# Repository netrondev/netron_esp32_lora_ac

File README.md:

# ESP32 LoRaWAN AC current monitor

A mains current monitor built on an ESP32 and an SX1262 radio. It measures AC
current through an ACS712 hall-effect sensor and reports it over LoRaWAN as an
OTAA Class A device. The repo also includes a small network server so you can
receive the reports and configure devices remotely, plus the KiCad hardware.

Everything is written in Rust except the payload codec, which is plain
JavaScript so it can be pasted into ChirpStack, The Things Network or Node-RED.

## How the pieces fit together

```
ACS712 current sensor
  └─ ESP32 + SX1262           firmware/           OTAA Class A device
       ~ 868.1 MHz SF7 ~
  └─ Milesight UG63 gateway                       Semtech UDP packet forwarder
       └─ software/lorans                         network server: joins, keys,
                                                  uplink decode, downlink queue
```

The gateway's own network server is **not** used. It has no usable downlink
route: there's no HTTP endpoint, and its MQTT application forwarder reboots the
gateway. Without downlinks there's no remote configuration. So the gateway runs
as a plain packet forwarder, and `software/lorans` does the network server's
job. `software/lorans/README.md` has the details.

Any gateway that speaks the Semtech UDP protocol should work in place of the
UG63. Alternatively, the devices can join a standard network server such as
ChirpStack, using the codec in `software/loradecode`.

| Directory | What it is |
|---|---|
| `firmware/` | ESP32 firmware. Measures current, joins by OTAA, reports aggregated min/avg/max, applies configuration downlinks |
| `software/lorans/` | Network server. Run this to receive uplinks and send commands |
| `software/loradecode/` | JavaScript payload decoder and command encoder for ChirpStack, TTN or Node-RED |
| `software/milesight_d4/` | Milesight gateway HTTP client: status, device list, forwarder mode, payload decode/encode |
| `software/loramqtt/` | Minimal MQTT broker, kept for diagnosing the gateway's MQTT forwarding |
| `docs/PROTOCOL.md` | Uplink channel map and downlink command set |
| `diagram/` | System overview: power supply, sensing, MCU and radio |
| `hardware/` | KiCad schematics, PCBs and JLCPCB fabrication outputs |
| `scripts/` | Build, flash and monitor helpers |

## Hardware

- **MCU:** ESP32 Mini32 (Wemos D1 Mini ESP32 form factor)
- **Radio:** Ai-Thinker Ra-01SH (SX1262), 868 MHz
- **Sensor:** ACS712-20A on GPIO34 through a voltage divider. RMS current is
  computed over one 50 Hz cycle of oversampled ADC readings
- **Power:** MB10S bridge rectifier into a BP2525 non-isolated buck, 5 V from
  230 V mains

| SX1262 | ESP32 |
|---|---|
| NSS | GPIO5 |
| RESET | GPIO27 |
| DIO1 | GPIO26 |
| SCK | GPIO18 |
| MISO | GPIO19 |
| MOSI | GPIO23 |

BUSY isn't wired to the ESP32. The driver waits a fixed settling time after
each command instead, and detects TxDone/RxDone from DIO1. The status LED is
on GPIO2.

> **Warning:** the power supply is non-isolated, so the whole board sits at
> mains potential. Don't touch it or connect USB while it's powered from
> mains.

## Device identity and keys

| | |
|---|---|
| DevEUI | Derived from the ESP32's MAC: `OUI FF FE NIC` |
| JoinEUI | `0000000000000000` |
| AppKey | The DevEUI repeated, e.g. `E08CFEFFFE34C3AC` → `E08CFEFFFE34C3ACE08CFEFFFE34C3AC` |

This follows the Milesight convention, so a device can be onboarded from
nothing but its join request. It also means **the AppKey is not a secret**.
That's fine for a private network on a private gateway. If you need real
over-the-air security, give each device a random AppKey. `docs/PROTOCOL.md`
covers this, along with the payload format.

## Getting started

### Toolchain

The ESP32 needs Rust's Xtensa toolchain. Install it with
[espup](https://github.com/esp-rs/espup), which writes `~/export-esp.sh`, then
install `espflash`:

```bash
cargo install espup espflash
espup install
```

Alternatively, build inside Docker with the image in `firmware/`. `scripts/build.sh`
and `scripts/flash.sh` use it:

```bash
docker build -t esp32-rust firmware/
```

### Flash and monitor a device

The scripts find the serial port automatically, or you can pass it explicitly:

```bash
./scripts/flash_native.sh            # host toolchain: build, flash, print the MAC
./scripts/flash.sh /dev/ttyUSB0      # same, building in Docker
./scripts/monitor.sh                 # serial monitor in Docker (CTRL+R resets, CTRL+C exits)
```

### Run the network server

Point the gateway's packet forwarder at this host on UDP port 1700, then start
the network server:

```bash
cargo run --manifest-path software/lorans/Cargo.toml
```

It accepts joins, decodes uplinks and queues downlinks. Commands go to a
control socket on `127.0.0.1:7788`. A queued downlink is sent in the receive
window after the device's next uplink. Intervals are in seconds:

```bash
echo 'downlink E08CFEFFFE34C3AC report=60 sample=5 jitter=10' | nc -q1 127.0.0.1 7788
echo 'list' | nc -q1 127.0.0.1 7788
```

### Milesight gateway

Copy `software/milesight_d4/config.json.example` to `config.json` and add the
gateway's address and login. Then:

```bash
cargo run --manifest-path software/milesight_d4/Cargo.toml -- status
cargo run --manifest-path software/milesight_d4/Cargo.toml -- set-forwarder semtech 192.168.1.100
```

## Firmware behaviour

- Joins by OTAA, retrying with exponential backoff
- Samples current every `sample` seconds and accumulates min/avg/max
- Sends one confirmed, aggregated report every `report` seconds, offset by a
  random ± `jitter` seconds so devices don't collide. An unacknowledged
  report is retried once
- Re-joins if the network stops acknowledging
- Applies configuration downlinks (intervals, jitter, reboot) and echoes each
  applied setting back as confirmation
- Keeps cumulative energy (mAh), frame counters, the join nonce and its
  configuration in flash across power cycles

### LED

| Pattern | Meaning |
|---|---|
| Short blink every ~0.5 s | Not joined yet, trying to join |
| Short blink per sample | Joined and measuring normally |
| Rapid triple blink | ADC error: sensor disconnected, or the reading saturated at 0 or 4095 |

## Troubleshooting

- **`xtensa-esp32-elf-gcc not found`:** run `source ~/export-esp.sh` first.
- **Permission denied on the serial port:** add yourself to the `dialout`
  group, or `sudo chmod 666 /dev/ttyUSB0`.
- **Device not found:** check `ls /dev/ttyUSB* /dev/ttyACM*`.
- **espflash asks for a chip or port inside Docker:** pass
  `--chip esp32 -p <port>` explicitly.
- **Flashing fails to connect:** hold BOOT while flashing, and release it
  after "Connecting...".

## License

Licensed under either of

- Apache License, Version 2.0 ([LICENSE-APACHE](LICENSE-APACHE))
- MIT license ([LICENSE-MIT](LICENSE-MIT))

at your option.

Unless you explicitly state otherwise, any contribution intentionally submitted
for inclusion in this work by you, as defined in the Apache-2.0 license, shall
be dual licensed as above, without any additional terms or conditions.

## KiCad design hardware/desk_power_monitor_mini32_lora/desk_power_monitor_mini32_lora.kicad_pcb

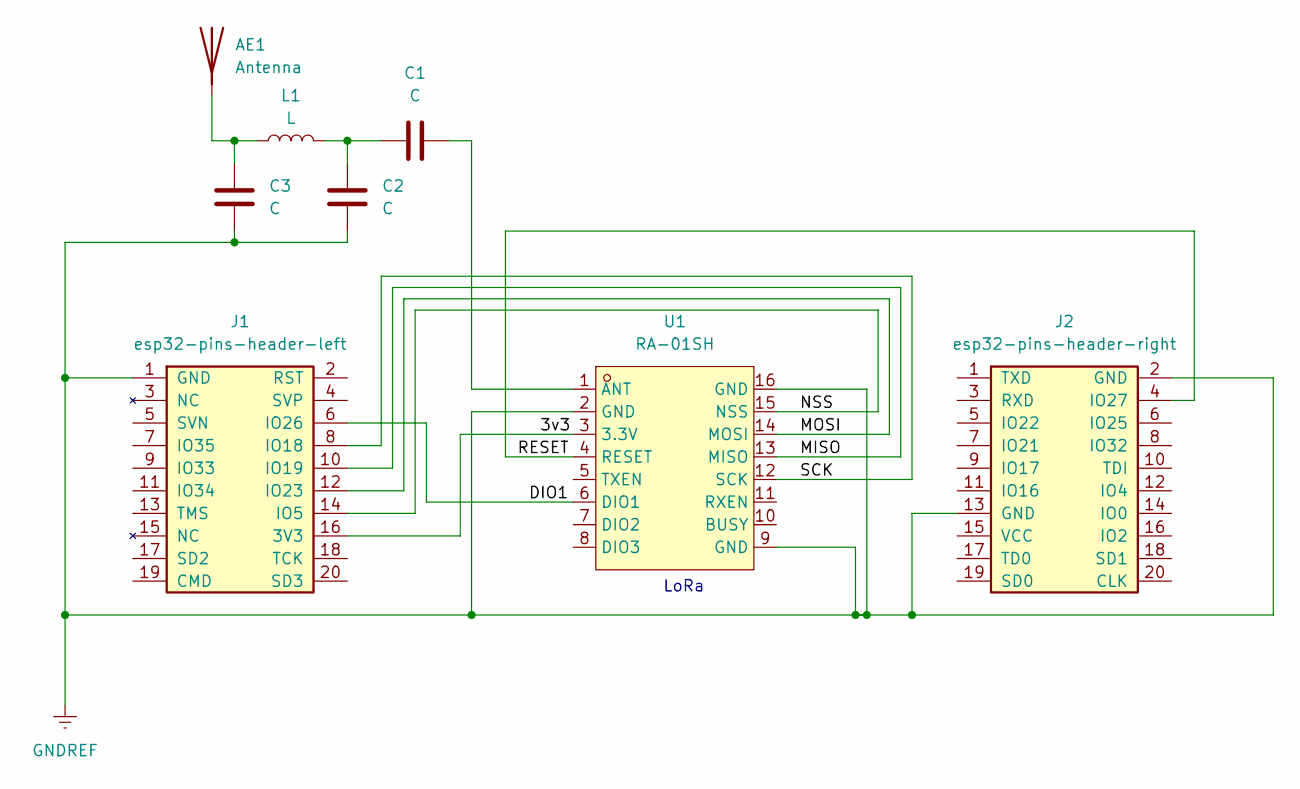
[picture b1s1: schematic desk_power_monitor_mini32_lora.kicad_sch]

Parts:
AE1: Antenna; Texas_SWRA416_868MHz_915MHz
C1, C2, C3: C; C_0805_2012Metric
J1: esp32-pins-header-left; PinHeader_2x10_P2.54mm_Vertical
J2: esp32-pins-header-right; PinHeader_2x10_P2.54mm_Vertical
L1: L; L_0805_2012Metric
U1: RA-01SH; WIRELM-SMD_RA-01SH; LCSC Part C2764087

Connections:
/3v3: J1.16 (3V3), U1.3 (3.3V)
/DIO1: J1.6 (IO26), U1.6 (DIO1)
/MISO: J1.10 (IO19), U1.13 (MISO)
/MOSI: J1.12 (IO23), U1.14 (MOSI)
/NSS: J1.14 (IO5), U1.15 (NSS)
/RESET: J2.4 (IO27), U1.4 (RESET)
/SCK: J1.8 (IO18), U1.12 (SCK)
GNDREF: C2.2, C3.2, J1.1 (GND), J2.2 (GND), J2.13 (GND), U1.2 (GND), U1.9 (GND), U1.16 (GND)
unnamed: AE1.1 (A), C3.1, L1.1
unnamed: C1.2, C2.1, L1.2
unnamed: C1.1, U1.1 (ANT)

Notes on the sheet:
LoRa

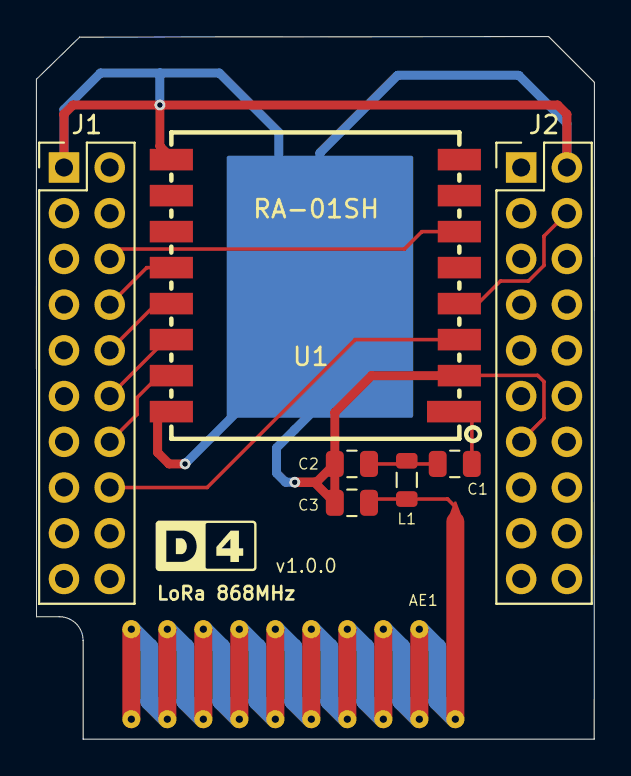
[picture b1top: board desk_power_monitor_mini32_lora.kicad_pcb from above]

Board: 2 copper layers, 31.0 x 39.0 mm, 8 parts (0 on the bottom side), 11 nets.

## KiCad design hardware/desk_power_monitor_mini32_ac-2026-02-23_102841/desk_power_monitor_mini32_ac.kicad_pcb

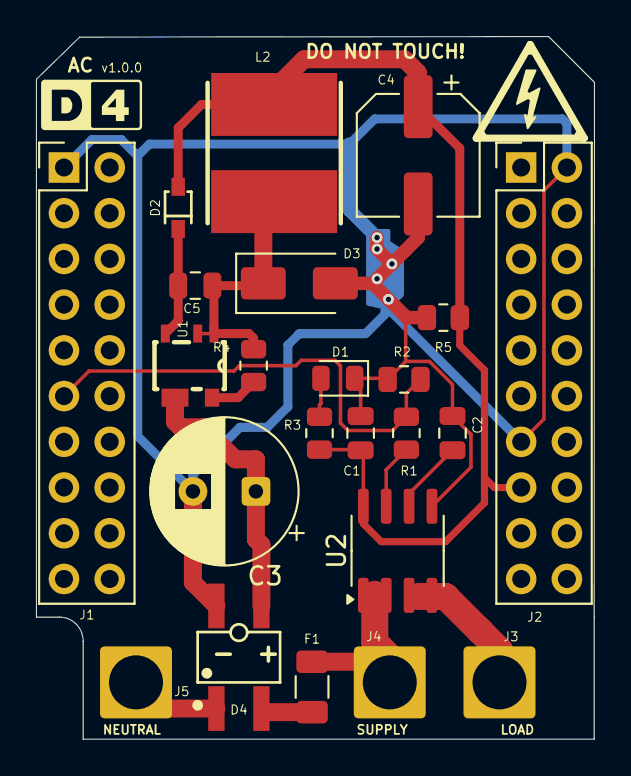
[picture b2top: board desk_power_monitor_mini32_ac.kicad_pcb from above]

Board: 2 copper layers, 31.0 x 39.0 mm, 23 parts (0 on the bottom side), 14 nets.

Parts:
C1, C5: 100nF; C_0805_2012Metric
C2: 1nF; C_0805_2012Metric
C3: 4.7µF / 400V electrolytic; CP_Radial_D8.0mm_P3.50mm
C4: 220uF/10V; CP_Elec_6.3x7.7
D1: LED; D_0805_2012Metric
D2: 1N4148WS-C57759; SOD-323_L1.8-W1.3-LS2.5-RD-1
D3: US1M; D_SMA
D4: MB10S(46MIL); MBS_L4.7-W4.0-P2.50-LS7.0-BL
F1: Fuse; Fuse_1206_3216Metric
J1: esp32-pins-header-left; PinHeader_2x10_P2.54mm_Vertical
J2: esp32-pins-header-right; PinHeader_2x10_P2.54mm_Vertical
J3: AC Live OUT; SolderWire-2.5sqmm_1x01_D2.4mm_OD3.6mm
J4: AC Live IN; SolderWire-2.5sqmm_1x01_D2.4mm_OD3.6mm
J5: AC Neutral IN; SolderWire-2.5sqmm_1x01_D2.4mm_OD3.6mm
L2: CY75-220UH; IND-SMD_L7.8-W7.0-A
R1, R2: 10k; R_0805_2012Metric
R3, R5: 1K; R_0805_2012Metric
R4: 0.68R; R_0805_2012Metric
U1: SOT33-5A_L3.9-W2.6-P0.90-BP2525D
U2: ACS712xLCTR-20A; SOIC-8_3.9x4.9mm_P1.27mm

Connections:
GNDREF: C1.1, C2.2, C3.2, C4.2, D1.1 (K), D3.2 (A), D4.4 (-), J1.1 (GND), J2.2 (GND), R2.1, R5.2, U2.5 (GND)
unnamed: D1.2 (A), R3.1
unnamed: C1.2, C4.1, D2.2 (A), J2.15 (VCC), L2.2, R3.2, R5.1, U2.8 (5V)
unnamed: C5.1, D2.1 (C), U1.3 (VCC)
unnamed: C5.2, D3.1 (K), L2.1, R4.2, U1.1 (GND), U1.2 (SEL)
unnamed: C3.1, D4.3 (+), U1.4 (DRAIN)
unnamed: D4.2 (AC), F1.2
unnamed: J1.11 (IO34), R1.2, R2.2
unnamed: J3.1, U2.3 (IP-), U2.4 (IP-)
unnamed: F1.1, J4.1, U2.1 (IP+), U2.2 (IP+)
unnamed: D4.1 (AC), J5.1
unnamed: R4.1, U1.5 (CS)
unnamed: C2.1, U2.6 (FILTER)
unnamed: R1.1, U2.7 (VIOUT)
